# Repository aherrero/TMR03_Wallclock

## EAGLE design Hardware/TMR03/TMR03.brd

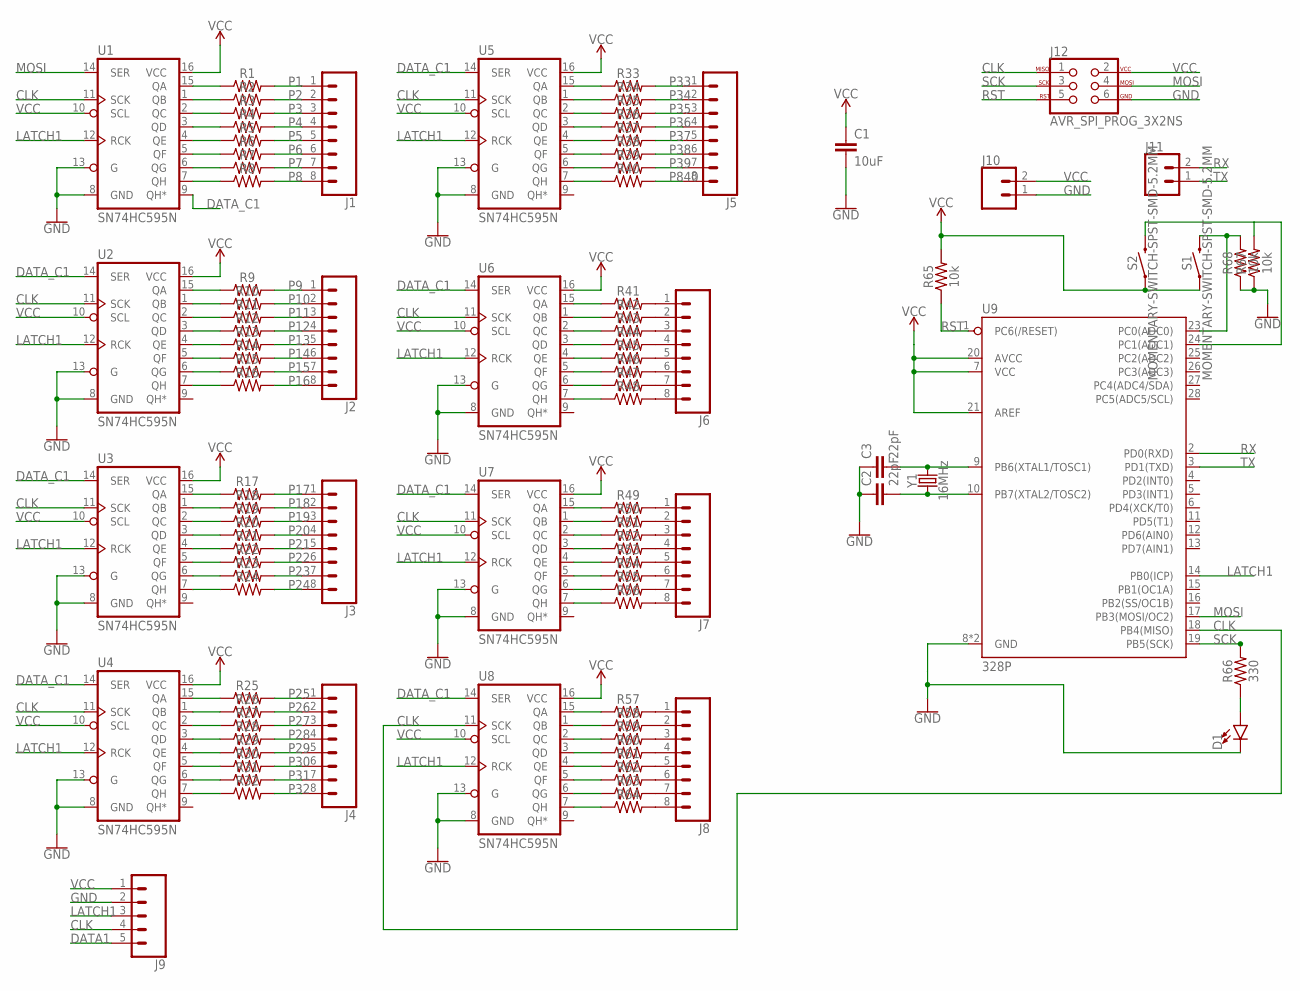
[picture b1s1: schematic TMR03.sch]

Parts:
C1: 10uF; 1206
C2, C3: 22pF; 1206
D1: LED3MM; LED_3MM
J1, J2, J3, J4, J5, J6, J7, J8: CONN_08"; 1X08
J9: CONN_05; 1X05
J10: CONN_02JST-PTH-2; JST-2-PTH
J11: CONN_02; 1X02
J12: AVR_SPI_PROG_3X2NS; 2X3-NS
R1, R2, R3, R4, R5, R6, R7, R8, R9, R10, R11, R12, R13, R14, R15, R16, R17, R18, R19, R20, R21, R22, R23, R24, R25, R26, R27, R28, R29, R30, R31, R32, R33, R34, R35, R36, R37, R38, R39, R40, R41, R42, R43, R44, R45, R46, R47, R48, R49, R50, R51, R52, R53, R54, R55, R56, R57, R58, R59, R60, R61, R62, R63, R64: 1206
R65, R67, R68: 10k; 1206
R66: 330; 1206
S1, S2: MOMENTARY-SWITCH-SPST-SMD-5.2MM; TACTILE_SWITCH_SMD_5.2MM
U1, U2, U3, U4, U5, U6, U7, U8: SN74HC595N; DIP16
U9: 328P; DIP28
Y1: 16MHz; HC49US

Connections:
CLK: J9.4, J12.1, U1.11 (SCK), U2.11 (SCK), U3.11 (SCK), U4.11 (SCK), U5.11 (SCK), U6.11 (SCK), U7.11 (SCK), U8.11 (SCK), U9.18 (PB4(MISO))
DATA1: J9.5
DATA_C1: U1.9 (QH*), U2.14 (SER), U3.14 (SER), U4.14 (SER), U5.14 (SER), U6.14 (SER), U7.14 (SER), U8.14 (SER)
GND: C1.2, C2.1, C3.1, J9.2, J10.1, J12.6, R67.1, R68.1, U1.8 (GND), U1.13 (G), U2.8 (GND), U2.13 (G), U3.8 (GND), U3.13 (G), U4.8 (GND), U4.13 (G), U5.8 (GND), U5.13 (G), U6.8 (GND), U6.13 (G), U7.8 (GND), U7.13 (G), U8.8 (GND), U8.13 (G)
LATCH1: J9.3, U1.12 (RCK), U2.12 (RCK), U3.12 (RCK), U4.12 (RCK), U5.12 (RCK), U6.12 (RCK), U7.12 (RCK), U8.12 (RCK), U9.14 (PB0(ICP))
MOSI: J12.4, U1.14 (SER), U9.17 (PB3(MOSI/OC2))
unnamed: R1.1, U1.15 (QA)
unnamed: R2.1, U1.1 (QB)
unnamed: R3.1, U1.2 (QC)
unnamed: R4.1, U1.3 (QD)
unnamed: R5.1, U1.4 (QE)
unnamed: R6.1, U1.5 (QF)
unnamed: R7.1, U1.6 (QG)
unnamed: R8.1, U1.7 (QH)
unnamed: R9.1, U2.15 (QA)
unnamed: R10.1, U2.1 (QB)
unnamed: R11.1, U2.2 (QC)
unnamed: R12.1, U2.3 (QD)
unnamed: R13.1, U2.4 (QE)
unnamed: R14.1, U2.5 (QF)
unnamed: R15.1, U2.6 (QG)
unnamed: R16.1, U2.7 (QH)
unnamed: R17.1, U3.15 (QA)
unnamed: R18.1, U3.1 (QB)
unnamed: R19.1, U3.2 (QC)
unnamed: R20.1, U3.3 (QD)
unnamed: R21.1, U3.4 (QE)
unnamed: R22.1, U3.5 (QF)
unnamed: R23.1, U3.6 (QG)
unnamed: R24.1, U3.7 (QH)
unnamed: R25.1, U4.15 (QA)
unnamed: R26.1, U4.1 (QB)
unnamed: R27.1, U4.2 (QC)
unnamed: R28.1, U4.3 (QD)
unnamed: R29.1, U4.4 (QE)
unnamed: R30.1, U4.5 (QF)
unnamed: R31.1, U4.6 (QG)
unnamed: R32.1, U4.7 (QH)
unnamed: R33.1, U5.15 (QA)
unnamed: R34.1, U5.1 (QB)
unnamed: R35.1, U5.2 (QC)
unnamed: R36.1, U5.3 (QD)
unnamed: R37.1, U5.4 (QE)
unnamed: R38.1, U5.5 (QF)
unnamed: R39.1, U5.6 (QG)
unnamed: R40.1, U5.7 (QH)
unnamed: R41.1, U6.15 (QA)
unnamed: R42.1, U6.1 (QB)
unnamed: R43.1, U6.2 (QC)
unnamed: R44.1, U6.3 (QD)
unnamed: R45.1, U6.4 (QE)
unnamed: R46.1, U6.5 (QF)
unnamed: R47.1, U6.6 (QG)
unnamed: R48.1, U6.7 (QH)
unnamed: R49.1, U7.15 (QA)
unnamed: R50.1, U7.1 (QB)
unnamed: R51.1, U7.2 (QC)
unnamed: R52.1, U7.3 (QD)
unnamed: R53.1, U7.4 (QE)
unnamed: R54.1, U7.5 (QF)
unnamed: R55.1, U7.6 (QG)
unnamed: R56.1, U7.7 (QH)
unnamed: R57.1, U8.15 (QA)
unnamed: R58.1, U8.1 (QB)
unnamed: R59.1, U8.2 (QC)
unnamed: R60.1, U8.3 (QD)
unnamed: R61.1, U8.4 (QE)
unnamed: R62.1, U8.5 (QF)
unnamed: R63.1, U8.6 (QG)
unnamed: R64.1, U8.7 (QH)
unnamed: J6.1, R41.2
unnamed: J6.2, R42.2
unnamed: J6.3, R43.2
unnamed: J6.4, R44.2
unnamed: J6.5, R45.2
unnamed: J6.6, R46.2
unnamed: J6.7, R47.2
unnamed: J6.8, R48.2
unnamed: J7.1, R49.2
unnamed: J7.2, R50.2
unnamed: J7.3, R51.2
unnamed: J7.4, R52.2
unnamed: J7.5, R53.2
unnamed: J7.6, R54.2
unnamed: J7.7, R55.2
unnamed: J7.8, R56.2
unnamed: J8.1, R57.2
unnamed: J8.2, R58.2
unnamed: J8.3, R59.2
unnamed: J8.4, R60.2
unnamed: J8.5, R61.2
unnamed: J8.6, R62.2
unnamed: J8.7, R63.2
unnamed: J8.8, R64.2
unnamed: C3.2, U9.9 (PB6(XTAL1/TOSC1)), Y1.2
unnamed: R68.2, S1.3 (2), U9.23 (PC0(ADC0))
unnamed: C2.2, U9.10 (PB7(XTAL2/TOSC2)), Y1.1
unnamed: R65.2, S1.1, S2.1
unnamed: U9.7 (VCC), U9.20 (AVCC), U9.21 (AREF)
unnamed: D1.K (C), U9.8 (GND), U9.22 (GND)
unnamed: R67.2, S2.3 (2), U9.24 (PC1(ADC1))
unnamed: D1.A, R66.1
P1: J1.1, R1.2
P2: J1.2, R2.2
P3: J1.3, R3.2
P4: J1.4, R4.2
P5: J1.5, R5.2
P6: J1.6, R6.2
P7: J1.7, R7.2
P8: J1.8, R8.2
P9: J2.1, R9.2
P10: J2.2, R10.2
P11: J2.3, R11.2
P12: J2.4, R12.2
P13: J2.5, R13.2
P14: J2.6, R14.2
P15: J2.7, R15.2
P16: J2.8, R16.2
P17: J3.1, R17.2
P18: J3.2, R18.2
P19: J3.3, R19.2
P20: J3.4, R20.2
P21: J3.5, R21.2
P22: J3.6, R22.2
P23: J3.7, R23.2
P24: J3.8, R24.2
P25: J4.1, R25.2
P26: J4.2, R26.2
P27: J4.3, R27.2
P28: J4.4, R28.2
P29: J4.5, R29.2
P30: J4.6, R30.2
P31: J4.7, R31.2
P32: J4.8, R32.2
P33: J5.1, R33.2
P34: J5.2, R34.2
P35: J5.3, R35.2
P36: J5.4, R36.2
P37: J5.5, R37.2
P38: J5.6, R38.2
P39: J5.7, R39.2
P840: J5.8, R40.2
RST: J12.5, R65.1, U9.1 (PC6(/RESET))
RX: J11.2, U9.2 (PD0(RXD))
SCK: J12.3, R66.2, U9.19 (PB5(SCK))
TX: J11.1, U9.3 (PD1(TXD))
VCC: C1.1, J9.1, J10.2, J12.2, U1.10 (SCL), U1.16 (VCC), U2.10 (SCL), U2.16 (VCC), U3.10 (SCL), U3.16 (VCC), U4.10 (SCL), U4.16 (VCC), U5.10 (SCL), U5.16 (VCC), U6.10 (SCL), U6.16 (VCC), U7.10 (SCL), U7.16 (VCC), U8.10 (SCL), U8.16 (VCC)

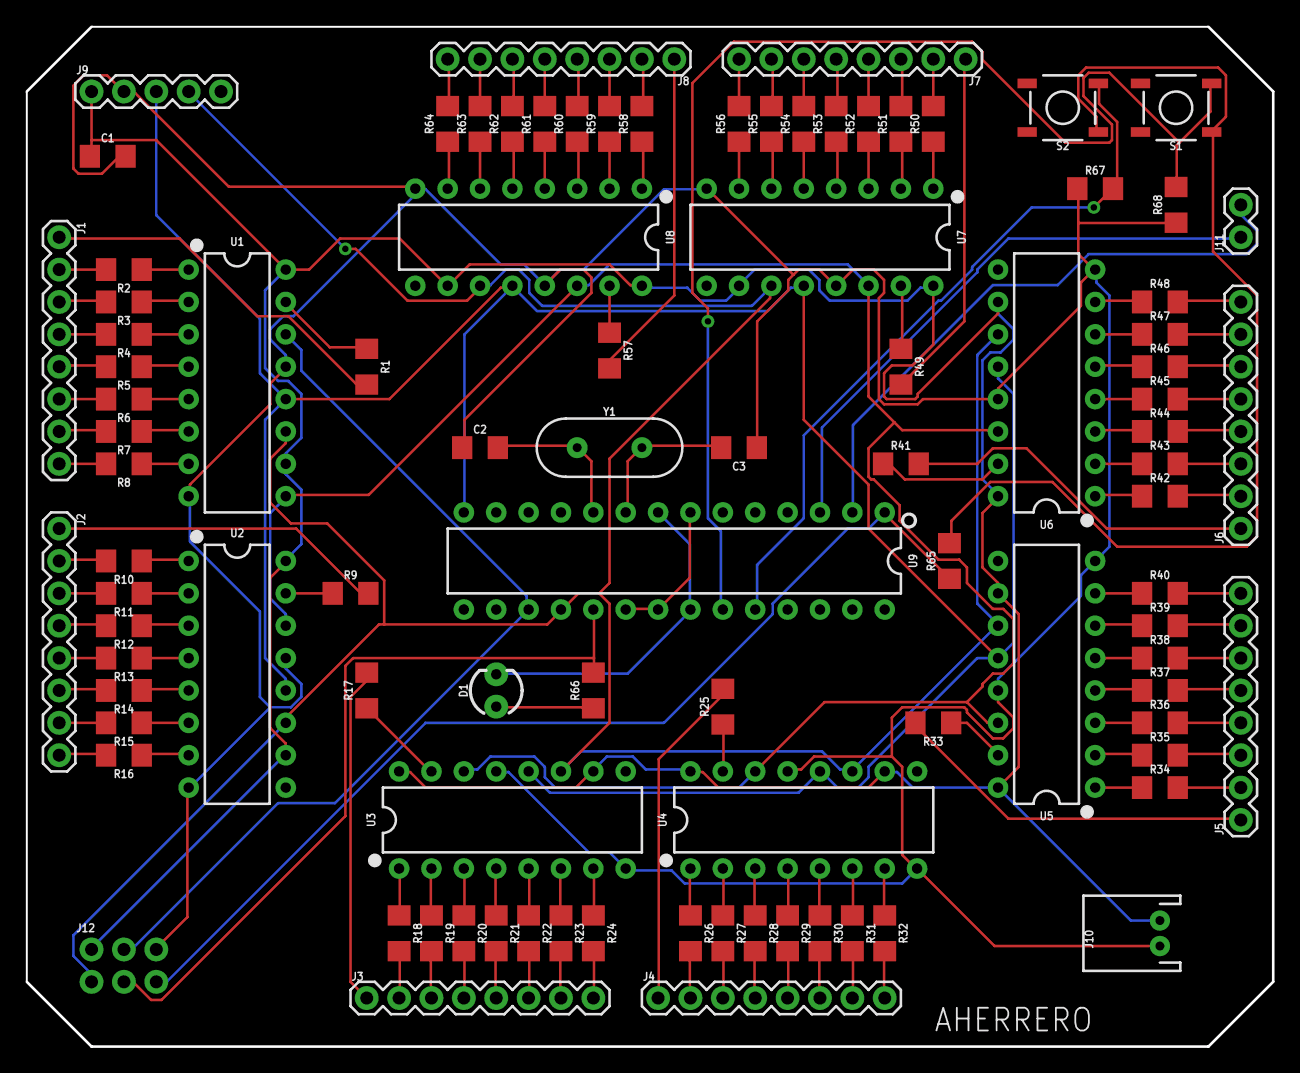
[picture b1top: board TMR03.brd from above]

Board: 2 copper layers, 97.8 x 80.0 mm, 96 parts (0 on the bottom side), 146 nets.

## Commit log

2018-11-16 first quick PCB for shift register cabling
2018-11-18 testing SW

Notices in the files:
parts and their libraries:
SparkFun-Connectors: Licensing: Creative Commons ShareAlike 4.0 International - https://creativecommons.org/licenses/by-sa/4.0
